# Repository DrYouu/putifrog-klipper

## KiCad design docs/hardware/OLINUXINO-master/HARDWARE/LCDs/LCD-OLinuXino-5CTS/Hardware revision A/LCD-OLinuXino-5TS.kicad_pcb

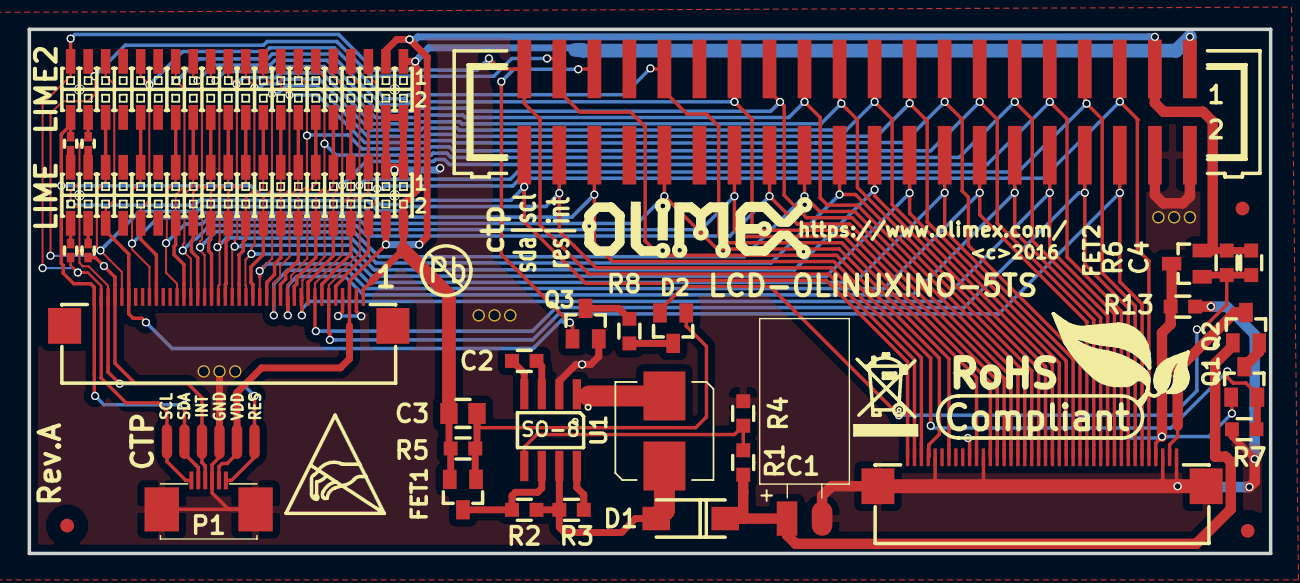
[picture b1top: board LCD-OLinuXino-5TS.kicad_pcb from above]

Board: 2 copper layers, 90.0 x 38.0 mm, 44 parts (0 on the bottom side), 54 nets.

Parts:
C1: 100uF/35V; CAP-EL-H-12x6.5
C2: 470pF; C_0603_5MIL_DWS
C3: 22uF/6.3V; C_0805_5MIL_DWS
C4: 1uF/6.3V; C_0603_5MIL_DWS
D1: 1N5819S(SS14); SMA-KA
D2: BAT54C; SOT23
FET1, FET2: IRML6402; SOT23
L1: 220uH/SD75; SD75
P1: CONN_01X06; FPV-WZB21-6-LF
P2: CONN_02X20; GBH-254-SMT-40
P3, P4: CONN_02X20; GPH127SMT-02X20(PA-V16X-2X20-LF)
P5, P6: CONN_01X40; FPV-WZA21-40-LF
P7: CONN_01X06; SIP6_SMD_50
Q1, Q3: DTC114YKA; SOT23
Q2: DTA114YKA; SOT23
R1, R5, R6, R13: 18K/1%; R_0603_5MIL_DWS
R2: 1R; R_0603_5MIL_DWS
R3: 150R; R_0603_5MIL_DWS
R4, R7, R8: 1.2K/1%; R_0603_5MIL_DWS
R9, R10, R11, R12: n.a(0R); J_0402_DWS
Ref**: Val**; via_09_07
Ref**#2, Ref**#3, Ref**#4, Ref**#5, Ref**#6, Ref**#7, Ref**#8, Ref**#9: Val**; via_09_07
Ref**#10: Val**; LOGO_ANTISTATIC_1
Ref**#11: Val**; LOGO_ROHS_1
U1: MC34063; SO-8

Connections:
+3.3VP: FET2.3, P6.4, P6.31, Q1.1, R13.1
/3.3V: C4.1, FET2.2, P1.2, P2.3, P3.3, P4.4, P5.3, P7.2, R6.1
/5V: C3.1, FET1.2, P2.1, P3.1, P4.2, P5.1, R5.1
/CTP_INT: P1.4, P2.37, P3.37, P5.37, P6.37, P7.4, R9.2
/CTP_RES: P1.1, P2.38, P3.38, P5.38, P6.38, P7.1, R10.1
/CTP_SCL: P1.6, P2.39, P3.39, P5.39, P6.39, P7.6, R11.2
/CTP_SDA: P1.5, P2.40, P3.40, P5.40, P6.40, P7.5, R12.1
/LCD_B0: P2.21, P3.21, P4.22, P5.21, P6.21
/LCD_B1: P2.22, P3.22, P4.21, P5.22, P6.22
/LCD_B2: P2.23, P3.23, P4.24, P5.23, P6.23
/LCD_B3: P2.24, P3.24, P4.23, P5.24, P6.24
/LCD_B4: P2.25, P3.25, P4.26, P5.25, P6.25
/LCD_B5: P2.26, P3.26, P4.25, P5.26, P6.26
/LCD_B6: P2.27, P3.27, P4.28, P5.27, P6.27
/LCD_B7: P2.28, P3.28, P4.27, P5.28, P6.28
/LCD_BKL: P2.36, P3.36, P4.35, P5.36, Q1.2, R7.1
/LCD_CLK: P2.31, P3.31, P4.32, P5.31, P6.30
/LCD_DE: P2.32, P3.32, P4.31, P5.32, P6.34
/LCD_G0: P2.13, P3.13, P4.14, P5.13, P6.13
/LCD_G1: P2.14, P3.14, P4.13, P5.14, P6.14
/LCD_G2: P2.15, P3.15, P4.16, P5.15, P6.15
/LCD_G3: P2.16, P3.16, P4.15, P5.16, P6.16
/LCD_G4: P2.17, P3.17, P4.18, P5.17, P6.17
/LCD_G5: P2.18, P3.18, P4.17, P5.18, P6.18
/LCD_G6: P2.19, P3.19, P4.20, P5.19, P6.19
/LCD_G7: P2.20, P3.20, P4.19, P5.20, P6.20
/LCD_PWRE: P2.35, P3.35, P4.36, P5.35, Q3.1
/LCD_R0: P2.5, P3.5, P4.6, P5.5, P6.5
/LCD_R1: P2.6, P3.6, P4.5, P5.6, P6.6
/LCD_R2: P2.7, P3.7, P4.8, P5.7, P6.7
/LCD_R3: P2.8, P3.8, P4.7, P5.8, P6.8
/LCD_R4: P2.9, P3.9, P4.10, P5.9, P6.9
/LCD_R5: P2.10, P3.10, P4.9, P5.10, P6.10
/LCD_R6: P2.11, P3.11, P4.12, P5.11, P6.11
/LCD_R7: P2.12, P3.12, P4.11, P5.12, P6.12
GND: C1.2, P1.3, P1.P1, P1.P2, P2.2, P2.4, P3.2, P3.4, P4.1, P4.3, P5.2, P5.4, P6.1, P6.3, P6.29, P6.36, P6.P1, P6.P2, P7.3, Q3.2, R4.2, R7.2, R13.2, Ref**.0, Ref**#2.0, Ref**#3.0, Ref**#4.0, Ref**#5.0, Ref**#6.0, Ref**#7.0, Ref**#8.0, Ref**#9.0, U1.2
unnamed: C1.1, D1.1, Q2.1, R1.1
unnamed: C2.1, U1.3
unnamed: C2.2, U1.4
unnamed: C3.2, D2.1, FET1.1, R5.2
unnamed: C4.2, D2.2, FET2.1, R6.2
unnamed: D1.2, L1.1, R2.2, R3.1, U1.7
unnamed: D2.3, R8.1
unnamed: L1.2, U1.1
unnamed: P4.37, R10.2
unnamed: P4.38, R9.1
unnamed: P4.39, R12.2
unnamed: P4.40, R11.1
unnamed: Q1.3, Q2.2
unnamed: Q3.3, R8.2
unnamed: R1.2, R4.1, U1.5
unnamed: R3.2, U1.8
VCOM: FET1.3, R2.1, U1.6
VLED: P6.2, Q2.3

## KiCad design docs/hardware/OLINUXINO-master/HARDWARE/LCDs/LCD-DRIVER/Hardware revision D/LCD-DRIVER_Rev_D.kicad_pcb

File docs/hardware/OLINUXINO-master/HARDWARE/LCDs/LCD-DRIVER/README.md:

LCD-DRIVER is a common LCD board used in some Olimex displays. It is important to notice that depending on the size of the display and the type of touschreen 
used the LCD_DRIVER board would be configured dirrently. Refer to the labes in the schematic and also refer to the bill of materials (BOM) for the different configurations.

List of boards using LCD-DRIVER as of 09.07.2025:

- LCD-OLinuXino-4.3RTS

- LCD-OLinuXino-7CTS

- LCD-OLinuXino-7RTS

- LCD-OLinuXino-10

- LCD-OLinuXino-10CTS

- LCD-OLinuXino-10RTS

All other LCDs use specific own specific boards (e.g. not LCD-DRIVER).

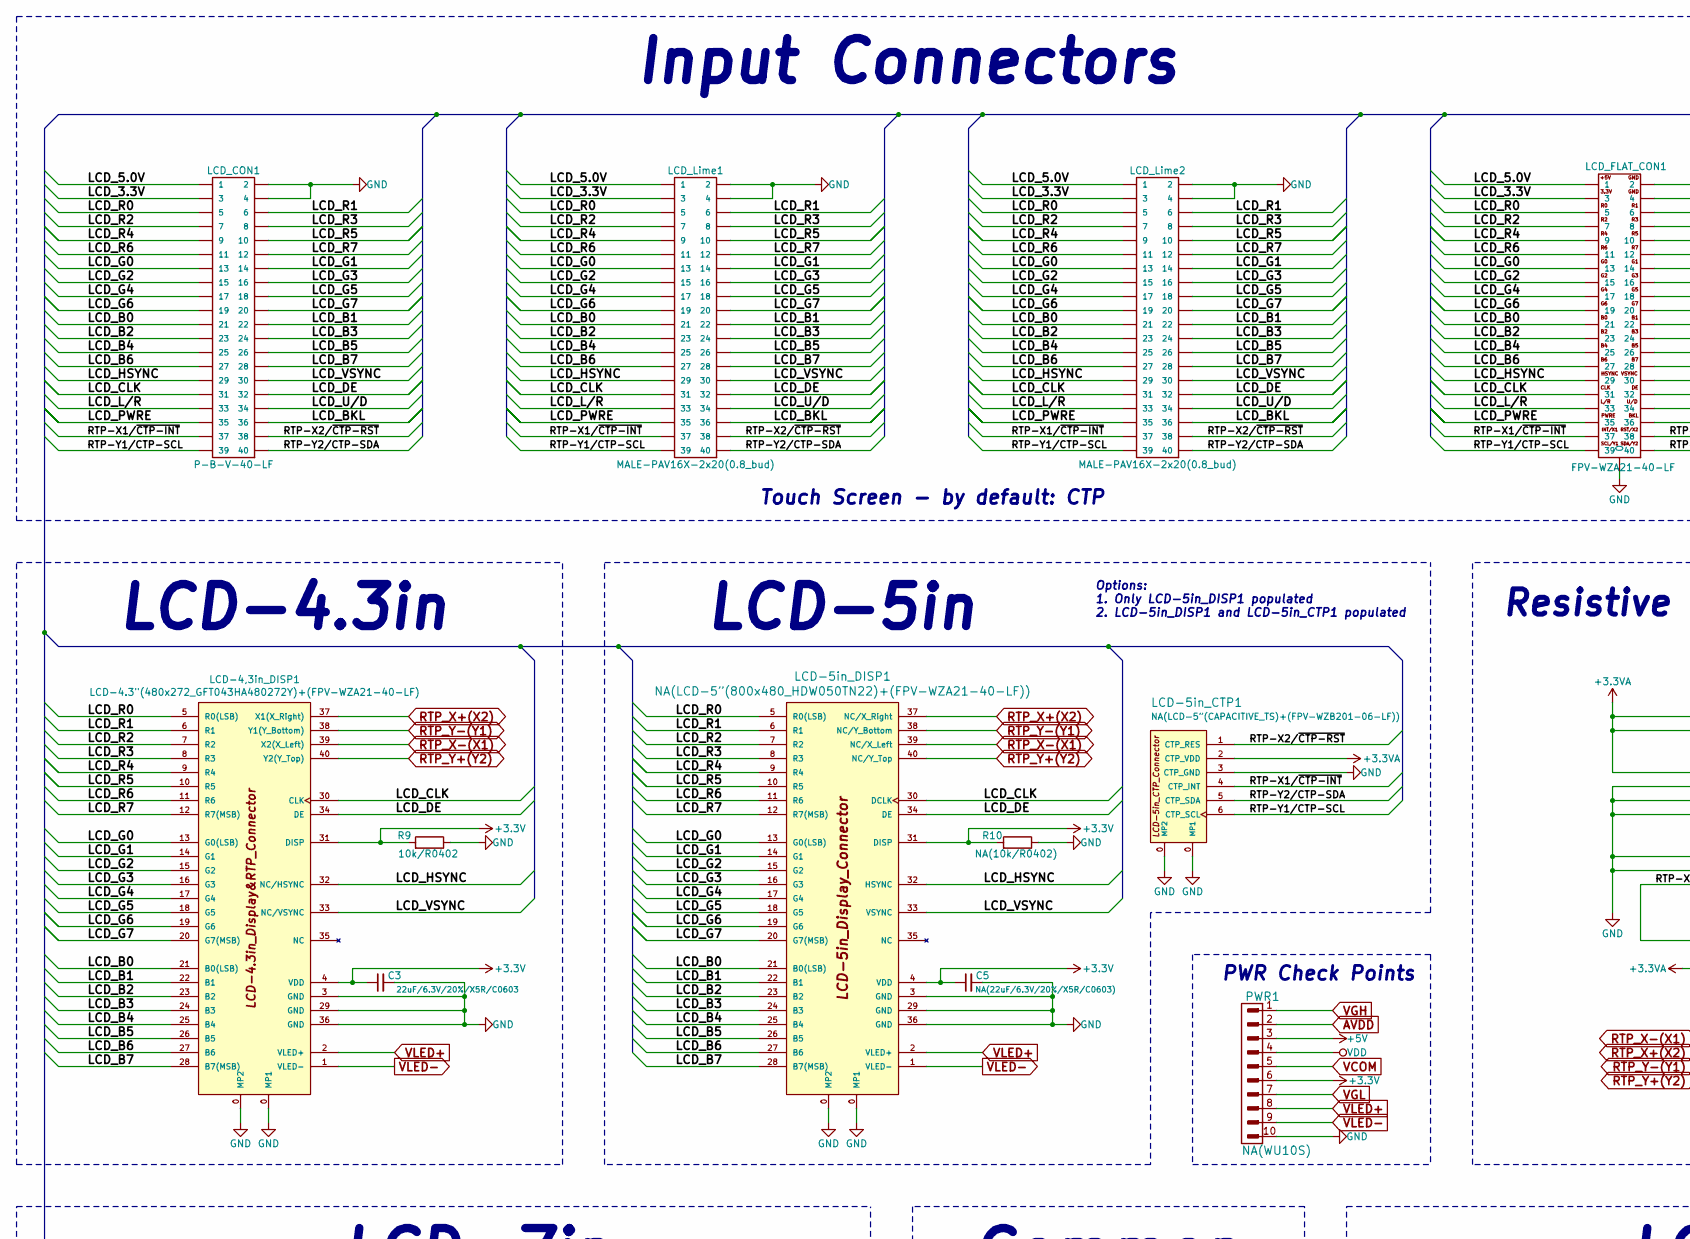
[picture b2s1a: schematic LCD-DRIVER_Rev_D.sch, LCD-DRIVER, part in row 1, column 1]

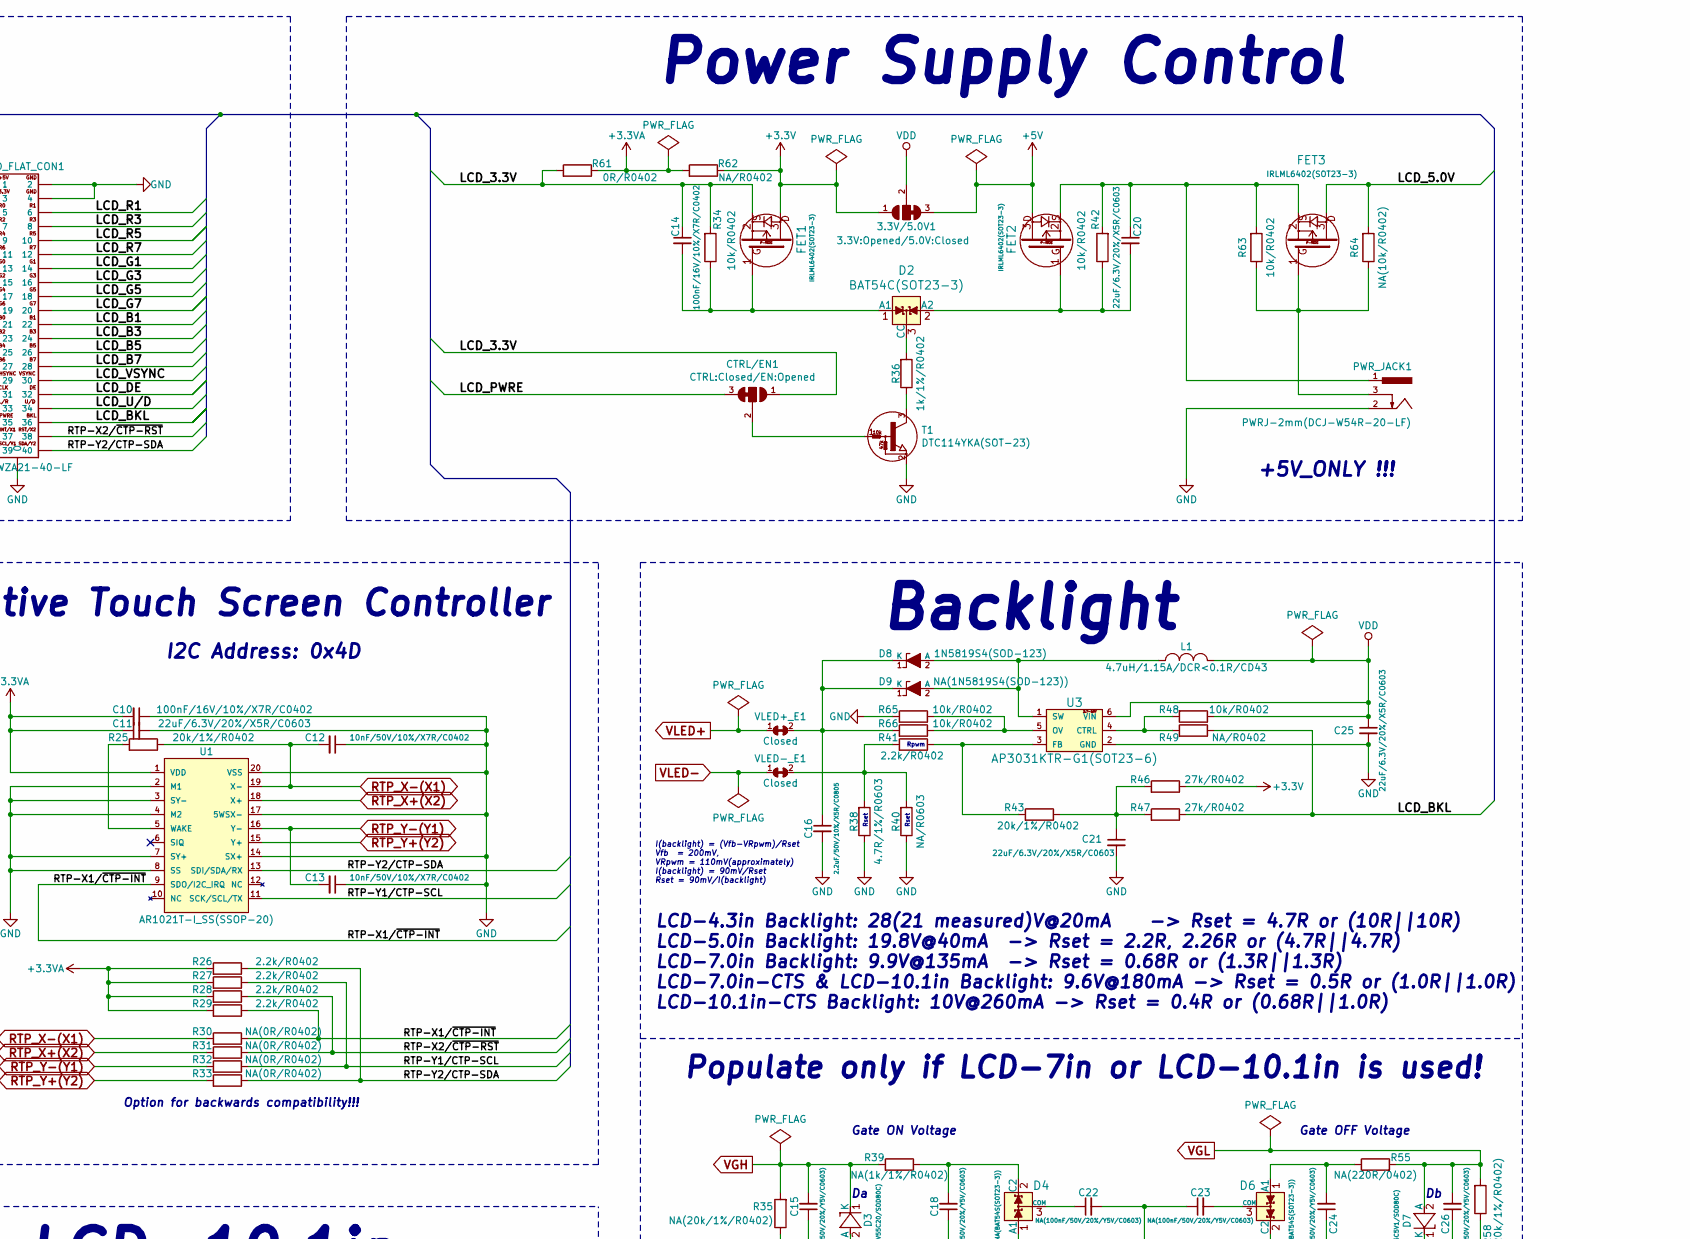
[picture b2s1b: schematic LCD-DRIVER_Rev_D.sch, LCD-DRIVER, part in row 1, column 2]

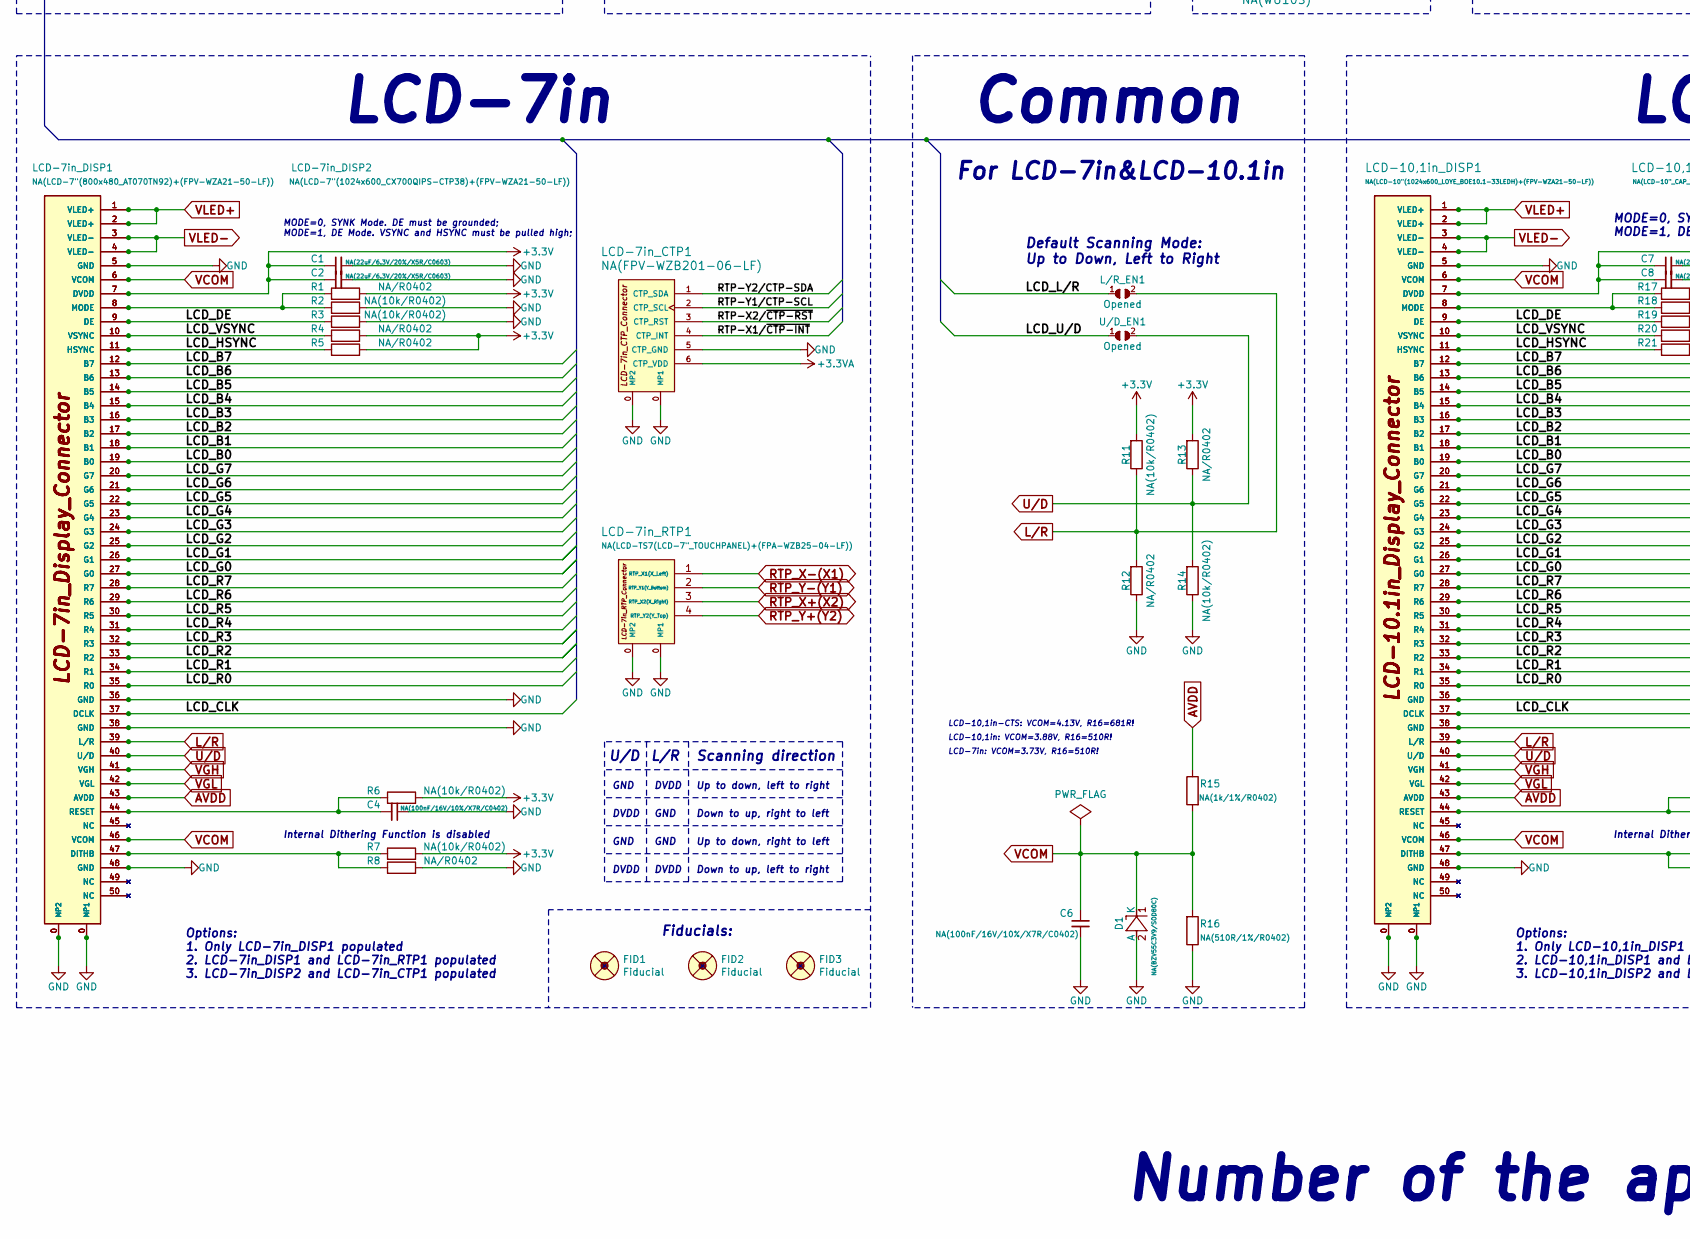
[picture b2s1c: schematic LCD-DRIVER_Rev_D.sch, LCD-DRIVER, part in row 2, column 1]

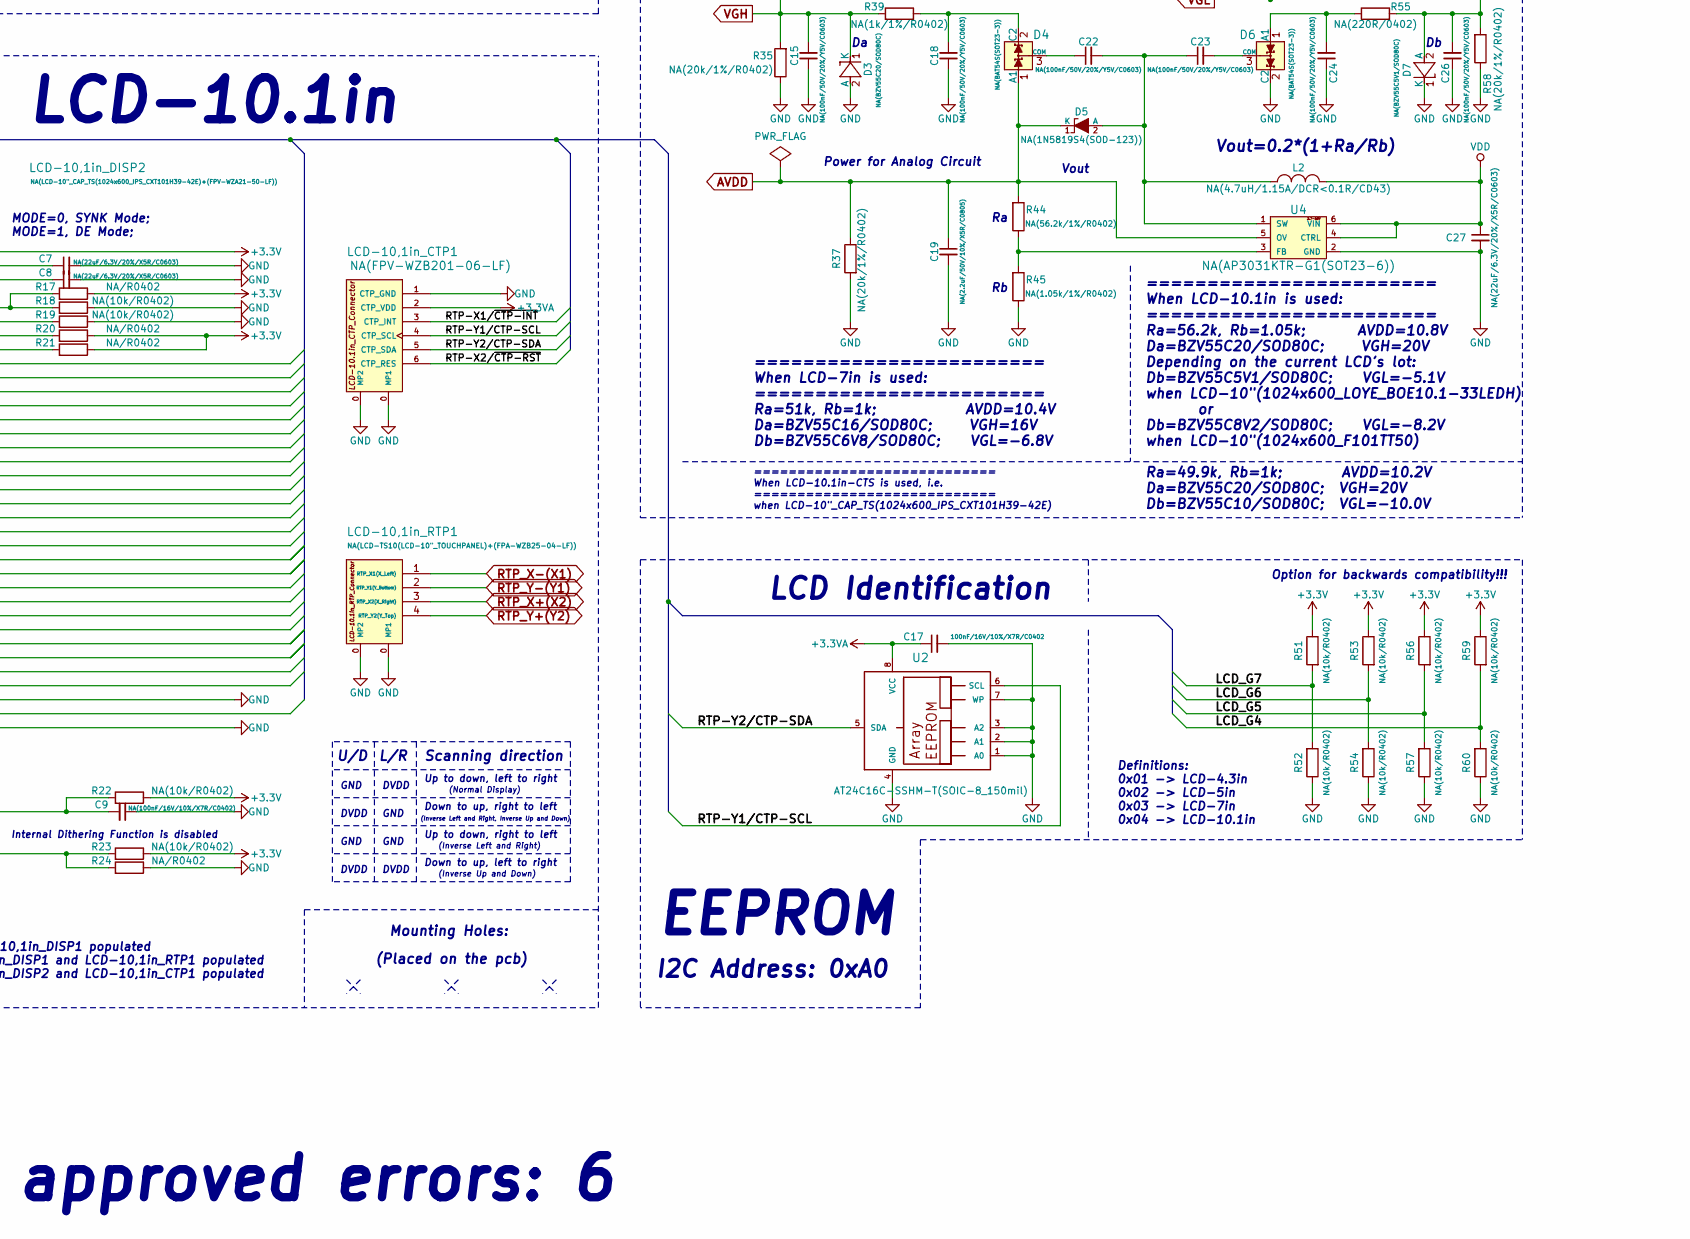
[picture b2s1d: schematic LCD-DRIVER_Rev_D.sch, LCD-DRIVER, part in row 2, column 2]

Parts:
3.3V/5.0V1: 3.3V:Opened/5.0V:Closed; SJ_2_SMALL_23_TIED
C1, C2, C5, C7, C8, C27: NA(22uF/6.3V/20%/X5R/C0603); C_0603_5MIL_DWS
C3, C11, C20, C21, C25: 22uF/6.3V/20%/X5R/C0603; C_0603_5MIL_DWS
C4, C6, C9: NA(100nF/16V/10%/X7R/C0402); C_0402_5MIL_DWS
C10, C14, C17: 100nF/16V/10%/X7R/C0402; C_0402_5MIL_DWS
C12, C13: 10nF/50V/10%/X7R/C0402; C_0402_5MIL_DWS
C15, C18, C22, C23, C24, C26: NA(100nF/50V/20%/Y5V/C0603); C_0603_5MIL_DWS
C16: 2.2uF/50V/10%/X5R/C0805; C_0805_5MIL_DWS
C19: NA(2.2uF/50V/10%/X5R/C0805); C_0805_5MIL_DWS
CTRL/EN1: CTRL:Closed/EN:Opened; SJ_2_SMALL_23_TIED
D1: NA(BZV55C3V9/SOD80C); SOD80C-4148-KA
D2: BAT54C(SOT23-3); SOT23-3
D3: NA(BZV55C20/SOD80C); SOD80C-4148-KA
D4, D6: NA(BAT54S(SOT23-3)); SOT23-3
D5, D9: NA(1N5819S4(SOD-123)); SOD-123_1C-2A_KA
D7: NA(BZV55C5V1/SOD80C); SOD80C-4148-KA
D8: 1N5819S4(SOD-123); SOD-123_1C-2A_KA
FET1, FET2, FET3: IRLML6402(SOT23-3); SOT23
FID1, FID2, FID3: Fiducial; Fiducial1x3
L1: 4.7uH/1.15A/DCR<0.1R/CD43; CD42(43)
L2: NA(4.7uH/1.15A/DCR<0.1R/CD43); CD42(43)
L/R_EN1: Opened; SJ
LCD-4,3in_DISP1: LCD-4.3\"(480x272_GFT043HA480272Y)+(FPV-WZA21-40-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; FPV-WZA21-40-LF
LCD-5in_CTP1: NA(LCD-5”(CAPACITIVE_TS)+(FPV-WZB201-06-LF)); FPV-WZB201-06-LF
LCD-5in_DISP1: NA(LCD-5”(800x480_HDW050TN22)+(FPV-WZA21-40-LF)); FPV-WZA21-40-LF
LCD-7in_CTP1, LCD-10,1in_CTP1: NA(FPV-WZB201-06-LF); FPV-WZB201-06-LF
LCD-7in_DISP1: NA(LCD-7\"(800x480_AT070TN92)+(FPV-WZA21-50-LF)); FPV-WZA21-50-LF
LCD-7in_DISP2: NA(LCD-7\"(1024x600_CX700QIPS-CTP38)+(FPV-WZA21-5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; FPV-WZA21-50-LF
LCD-7in_RTP1: NA(LCD-TS7(LCD-7\"_TOUCHPANEL)+(FPA-WZB25-04-LF)); FPA-WZB25-04-LF
LCD-10,1in_DISP1: NA(LCD-10\"(1024x600_LOYE_BOE10.1-33LEDH)+(FPV-WZ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; FPV-WZA21-50-LF
LCD-10,1in_DISP2: NA(LCD-10\"_CAP_TS(1024x600_IPS_CXT101H39-42E)+(F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; FPV-WZA21-50-LF
LCD-10,1in_RTP1: NA(LCD-TS10(LCD-10\"_TOUCHPANEL)+(FPA-WZB25-04-LF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; FPA-WZB25-04-LF
LCD_CON1: P-B-V-40-LF; GBH254SMT-40
LCD_FLAT_CON1: FPV-WZA21-40-LF
LCD_Lime1: MALE-PAV16X-2x20(0.8_bud); GPCB127SMT-02X20(YA-V36P-2X20-LF)_Drill_0.9mm
LCD_Lime2: MALE-PAV16X-2x20(0.8_bud); GPH127SMT-02X20(PA-V16X-2X20-LF)_Drill_0.9mm
PWR1: NA(WU10S); WU10S
PWR_JACK1: PWRJ-2mm(DCJ-W54R-20-LF)
R1, R4, R5, R8, R12, R13, R17, R20, R21, R24, R49, R62: NA/R0402; R_0402_5MIL_DWS
R2, R3, R6, R7, R10, R11, R14, R18, R19, R22, R23, R51, R52, R53, R54, R56, R57, R59, R60, R64: NA(10k/R0402); R_0402_5MIL_DWS
R9, R34, R42, R48, R63, R65, R66: 10k/R0402; R_0402_5MIL_DWS
R15, R39: NA(1k/1%/R0402); R_0402_5MIL_DWS
R16: NA(510R/1%/R0402); R_0402_5MIL_DWS
R25, R43: 20k/1%/R0402; R_0402_5MIL_DWS
R26, R27, R28, R29, R41: 2.2k/R0402; R_0402_5MIL_DWS
R30, R31, R32, R33: NA(0R/R0402); R_0402_5MIL_DWS
R35, R37, R58: NA(20k/1%/R0402); R_0402_5MIL_DWS
R36: 1k/1%/R0402; R_0402_5MIL_DWS
R38: 4.7R/1%/R0603; R_0603_5MIL_DWS
R40: NA/R0603; R_0603_5MIL_DWS
R44: NA(56.2k/1%/R0402); R_0402_5MIL_DWS
R45: NA(1.05k/1%/R0402); R_0402_5MIL_DWS
R46, R47: 27k/R0402; R_0402_5MIL_DWS
R55: NA(220R/0402); R_0402_5MIL_DWS
R61: 0R/R0402; R_0402_5MIL_DWS
T1: DTC114YKA(SOT-23); SOT23
U1: AR1021T-I_SS(SSOP-20); SSOP-20W
U2: AT24C16C-SSHM-T(SOIC-8_150mil); SOIC-8_150mil
U3: AP3031KTR-G1(SOT23-6); SOT23-6
U4: NA(AP3031KTR-G1(SOT23-6)); SOT23-6
U/D_EN1: Opened; SJ
VLED+_E1: Closed; SJ_Closed
VLED-_E1: Closed; SJ_Closed

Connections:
+3.3VA: C10.2, C11.1, C17.1, LCD-5in_CTP1.2 (CTP_VDD), LCD-7in_CTP1.6 (CTP_VDD), LCD-10,1in_CTP1.2 (CTP_VDD), R26.2, R27.2, R28.2, R29.2, R61.1, R62.2, U1.1 (VDD), U2.8 (VCC)
+3V3: 3.3V/5.0V1.1, C1.1, C2.1, C3.1, C5.1, C7.1, C8.1, FET1.3, LCD-4,3in_DISP1.4 (VDD), LCD-4,3in_DISP1.31 (DISP), LCD-5in_DISP1.4 (VDD), LCD-5in_DISP1.31 (DISP), LCD-7in_DISP1.7 (DVDD), LCD-7in_DISP2.7 (DVDD), LCD-10,1in_DISP1.7 (DVDD), LCD-10,1in_DISP2.7 (DVDD), PWR1.6, R1.1, R4.1, R5.1, R6.1, R7.1, R9.2, R10.2, R11.2, R13.2, R17.1, R20.1, R21.1, R22.1, R23.1, R46.1, R51.1, R53.1, R56.1, R59.1, R62.1
+5V: 3.3V/5.0V1.3, FET2.3, PWR1.3
/LCD_3.3V: C14.1, CTRL/EN1.1, FET1.2, LCD_CON1.3, LCD_FLAT_CON1.3, LCD_Lime1.3, LCD_Lime2.3, R34.2, R61.2
/LCD_5.0V: FET3.3, LCD_CON1.1, LCD_FLAT_CON1.1, LCD_Lime1.1, LCD_Lime2.1, R64.2
/LCD_B0: LCD-4,3in_DISP1.21 (B0(LSB)), LCD-5in_DISP1.21 (B0(LSB)), LCD-7in_DISP1.19 (B0), LCD-7in_DISP2.19 (B0), LCD-10,1in_DISP1.19 (B0), LCD-10,1in_DISP2.19 (B0), LCD_CON1.21, LCD_FLAT_CON1.21, LCD_Lime1.21, LCD_Lime2.21
/LCD_B1: LCD-4,3in_DISP1.22 (B1), LCD-5in_DISP1.22 (B1), LCD-7in_DISP1.18 (B1), LCD-7in_DISP2.18 (B1), LCD-10,1in_DISP1.18 (B1), LCD-10,1in_DISP2.18 (B1), LCD_CON1.22, LCD_FLAT_CON1.22, LCD_Lime1.22, LCD_Lime2.22
/LCD_B2: LCD-4,3in_DISP1.23 (B2), LCD-5in_DISP1.23 (B2), LCD-7in_DISP1.17 (B2), LCD-7in_DISP2.17 (B2), LCD-10,1in_DISP1.17 (B2), LCD-10,1in_DISP2.17 (B2), LCD_CON1.23, LCD_FLAT_CON1.23, LCD_Lime1.23, LCD_Lime2.23
/LCD_B3: LCD-4,3in_DISP1.24 (B3), LCD-5in_DISP1.24 (B3), LCD-7in_DISP1.16 (B3), LCD-7in_DISP2.16 (B3), LCD-10,1in_DISP1.16 (B3), LCD-10,1in_DISP2.16 (B3), LCD_CON1.24, LCD_FLAT_CON1.24, LCD_Lime1.24, LCD_Lime2.24
/LCD_B4: LCD-4,3in_DISP1.25 (B4), LCD-5in_DISP1.25 (B4), LCD-7in_DISP1.15 (B4), LCD-7in_DISP2.15 (B4), LCD-10,1in_DISP1.15 (B4), LCD-10,1in_DISP2.15 (B4), LCD_CON1.25, LCD_FLAT_CON1.25, LCD_Lime1.25, LCD_Lime2.25
/LCD_B5: LCD-4,3in_DISP1.26 (B5), LCD-5in_DISP1.26 (B5), LCD-7in_DISP1.14 (B5), LCD-7in_DISP2.14 (B5), LCD-10,1in_DISP1.14 (B5), LCD-10,1in_DISP2.14 (B5), LCD_CON1.26, LCD_FLAT_CON1.26, LCD_Lime1.26, LCD_Lime2.26
/LCD_B6: LCD-4,3in_DISP1.27 (B6), LCD-5in_DISP1.27 (B6), LCD-7in_DISP1.13 (B6), LCD-7in_DISP2.13 (B6), LCD-10,1in_DISP1.13 (B6), LCD-10,1in_DISP2.13 (B6), LCD_CON1.27, LCD_FLAT_CON1.27, LCD_Lime1.27, LCD_Lime2.27
/LCD_B7: LCD-4,3in_DISP1.28 (B7(MSB)), LCD-5in_DISP1.28 (B7(MSB)), LCD-7in_DISP1.12 (B7), LCD-7in_DISP2.12 (B7), LCD-10,1in_DISP1.12 (B7), LCD-10,1in_DISP2.12 (B7), LCD_CON1.28, LCD_FLAT_CON1.28, LCD_Lime1.28, LCD_Lime2.28
/LCD_BKL: LCD_CON1.36, LCD_FLAT_CON1.36, LCD_Lime1.36, LCD_Lime2.36, R47.1, R49.1
/LCD_CLK: LCD-4,3in_DISP1.30 (CLK), LCD-5in_DISP1.30 (DCLK), LCD-7in_DISP1.37 (DCLK), LCD-7in_DISP2.37 (DCLK), LCD-10,1in_DISP1.37 (DCLK), LCD-10,1in_DISP2.37 (DCLK), LCD_CON1.31, LCD_FLAT_CON1.31, LCD_Lime1.31, LCD_Lime2.31
/LCD_DE: LCD-4,3in_DISP1.34 (DE), LCD-5in_DISP1.34 (DE), LCD-7in_DISP1.9 (DE), LCD-7in_DISP2.9 (DE), LCD-10,1in_DISP1.9 (DE), LCD-10,1in_DISP2.9 (DE), LCD_CON1.32, LCD_FLAT_CON1.32, LCD_Lime1.32, LCD_Lime2.32, R3.2, R19.2
/LCD_G0: LCD-4,3in_DISP1.13 (G0(LSB)), LCD-5in_DISP1.13 (G0(LSB)), LCD-7in_DISP1.27 (G0), LCD-7in_DISP2.27 (G0), LCD-10,1in_DISP1.27 (G0), LCD-10,1in_DISP2.27 (G0), LCD_CON1.13, LCD_FLAT_CON1.13, LCD_Lime1.13, LCD_Lime2.13
/LCD_G1: LCD-4,3in_DISP1.14 (G1), LCD-5in_DISP1.14 (G1), LCD-7in_DISP1.26 (G1), LCD-7in_DISP2.26 (G1), LCD-10,1in_DISP1.26 (G1), LCD-10,1in_DISP2.26 (G1), LCD_CON1.14, LCD_FLAT_CON1.14, LCD_Lime1.14, LCD_Lime2.14
/LCD_G2: LCD-4,3in_DISP1.15 (G2), LCD-5in_DISP1.15 (G2), LCD-7in_DISP1.25 (G2), LCD-7in_DISP2.25 (G2), LCD-10,1in_DISP1.25 (G2), LCD-10,1in_DISP2.25 (G2), LCD_CON1.15, LCD_FLAT_CON1.15, LCD_Lime1.15, LCD_Lime2.15
/LCD_G3: LCD-4,3in_DISP1.16 (G3), LCD-5in_DISP1.16 (G3), LCD-7in_DISP1.24 (G3), LCD-7in_DISP2.24 (G3), LCD-10,1in_DISP1.24 (G3), LCD-10,1in_DISP2.24 (G3), LCD_CON1.16, LCD_FLAT_CON1.16, LCD_Lime1.16, LCD_Lime2.16
/LCD_G4: LCD-4,3in_DISP1.17 (G4), LCD-5in_DISP1.17 (G4), LCD-7in_DISP1.23 (G4), LCD-7in_DISP2.23 (G4), LCD-10,1in_DISP1.23 (G4), LCD-10,1in_DISP2.23 (G4), LCD_CON1.17, LCD_FLAT_CON1.17, LCD_Lime1.17, LCD_Lime2.17, R59.2, R60.2
/LCD_G5: LCD-4,3in_DISP1.18 (G5), LCD-5in_DISP1.18 (G5), LCD-7in_DISP1.22 (G5), LCD-7in_DISP2.22 (G5), LCD-10,1in_DISP1.22 (G5), LCD-10,1in_DISP2.22 (G5), LCD_CON1.18, LCD_FLAT_CON1.18, LCD_Lime1.18, LCD_Lime2.18, R56.2, R57.2
/LCD_G6: LCD-4,3in_DISP1.19 (G6), LCD-5in_DISP1.19 (G6), LCD-7in_DISP1.21 (G6), LCD-7in_DISP2.21 (G6), LCD-10,1in_DISP1.21 (G6), LCD-10,1in_DISP2.21 (G6), LCD_CON1.19, LCD_FLAT_CON1.19, LCD_Lime1.19, LCD_Lime2.19, R53.2, R54.2
/LCD_G7: LCD-4,3in_DISP1.20 (G7(MSB)), LCD-5in_DISP1.20 (G7(MSB)), LCD-7in_DISP1.20 (G7), LCD-7in_DISP2.20 (G7), LCD-10,1in_DISP1.20 (G7), LCD-10,1in_DISP2.20 (G7), LCD_CON1.20, LCD_FLAT_CON1.20, LCD_Lime1.20, LCD_Lime2.20, R51.2, R52.2
/LCD_HSYNC: LCD-4,3in_DISP1.32 (NC/HSYNC), LCD-5in_DISP1.32 (HSYNC), LCD-7in_DISP1.11 (HSYNC), LCD-7in_DISP2.11 (HSYNC), LCD-10,1in_DISP1.11 (HSYNC), LCD-10,1in_DISP2.11 (HSYNC), LCD_CON1.29, LCD_FLAT_CON1.29, LCD_Lime1.29, LCD_Lime2.29, R5.2, R21.2
/LCD_L/R: L/R_EN1.1, LCD_CON1.33, LCD_FLAT_CON1.33, LCD_Lime1.33, LCD_Lime2.33
/LCD_PWRE: CTRL/EN1.3, LCD_CON1.35, LCD_FLAT_CON1.35, LCD_Lime1.35, LCD_Lime2.35
/LCD_R0: LCD-4,3in_DISP1.5 (R0(LSB)), LCD-5in_DISP1.5 (R0(LSB)), LCD-7in_DISP1.35 (R0), LCD-7in_DISP2.35 (R0), LCD-10,1in_DISP1.35 (R0), LCD-10,1in_DISP2.35 (R0), LCD_CON1.5, LCD_FLAT_CON1.5, LCD_Lime1.5, LCD_Lime2.5
/LCD_R1: LCD-4,3in_DISP1.6 (R1), LCD-5in_DISP1.6 (R1), LCD-7in_DISP1.34 (R1), LCD-7in_DISP2.34 (R1), LCD-10,1in_DISP1.34 (R1), LCD-10,1in_DISP2.34 (R1), LCD_CON1.6, LCD_FLAT_CON1.6, LCD_Lime1.6, LCD_Lime2.6
/LCD_R2: LCD-4,3in_DISP1.7 (R2), LCD-5in_DISP1.7 (R2), LCD-7in_DISP1.33 (R2), LCD-7in_DISP2.33 (R2), LCD-10,1in_DISP1.33 (R2), LCD-10,1in_DISP2.33 (R2), LCD_CON1.7, LCD_FLAT_CON1.7, LCD_Lime1.7, LCD_Lime2.7
/LCD_R3: LCD-4,3in_DISP1.8 (R3), LCD-5in_DISP1.8 (R3), LCD-7in_DISP1.32 (R3), LCD-7in_DISP2.32 (R3), LCD-10,1in_DISP1.32 (R3), LCD-10,1in_DISP2.32 (R3), LCD_CON1.8, LCD_FLAT_CON1.8, LCD_Lime1.8, LCD_Lime2.8
/LCD_R4: LCD-4,3in_DISP1.9 (R4), LCD-5in_DISP1.9 (R4), LCD-7in_DISP1.31 (R4), LCD-7in_DISP2.31 (R4), LCD-10,1in_DISP1.31 (R4), LCD-10,1in_DISP2.31 (R4), LCD_CON1.9, LCD_FLAT_CON1.9, LCD_Lime1.9, LCD_Lime2.9
/LCD_R5: LCD-4,3in_DISP1.10 (R5), LCD-5in_DISP1.10 (R5), LCD-7in_DISP1.30 (R5), LCD-7in_DISP2.30 (R5), LCD-10,1in_DISP1.30 (R5), LCD-10,1in_DISP2.30 (R5), LCD_CON1.10, LCD_FLAT_CON1.10, LCD_Lime1.10, LCD_Lime2.10
/LCD_R6: LCD-4,3in_DISP1.11 (R6), LCD-5in_DISP1.11 (R6), LCD-7in_DISP1.29 (R6), LCD-7in_DISP2.29 (R6), LCD-10,1in_DISP1.29 (R6), LCD-10,1in_DISP2.29 (R6), LCD_CON1.11, LCD_FLAT_CON1.11, LCD_Lime1.11, LCD_Lime2.11
/LCD_R7: LCD-4,3in_DISP1.12 (R7(MSB)), LCD-5in_DISP1.12 (R7(MSB)), LCD-7in_DISP1.28 (R7), LCD-7in_DISP2.28 (R7), LCD-10,1in_DISP1.28 (R7), LCD-10,1in_DISP2.28 (R7), LCD_CON1.12, LCD_FLAT_CON1.12, LCD_Lime1.12, LCD_Lime2.12
/LCD_U/D: LCD_CON1.34, LCD_FLAT_CON1.34, LCD_Lime1.34, LCD_Lime2.34, U/D_EN1.1
/LCD_VSYNC: LCD-4,3in_DISP1.33 (NC/VSYNC), LCD-5in_DISP1.33 (VSYNC), LCD-7in_DISP1.10 (VSYNC), LCD-7in_DISP2.10 (VSYNC), LCD-10,1in_DISP1.10 (VSYNC), LCD-10,1in_DISP2.10 (VSYNC), LCD_CON1.30, LCD_FLAT_CON1.30, LCD_Lime1.30, LCD_Lime2.30, R4.2, R20.2
/RTP-X1/~CTP-INT: LCD-5in_CTP1.4 (CTP_INT), LCD-7in_CTP1.4 (CTP_INT), LCD-10,1in_CTP1.3 (CTP_INT), LCD_CON1.37, LCD_FLAT_CON1.37, LCD_Lime1.37, LCD_Lime2.37, R29.1, R30.1, U1.9 (SDO/I2C_IRQ)
/RTP-X2/~CTP-RST: LCD-5in_CTP1.1 (CTP_RES), LCD-7in_CTP1.3 (CTP_RST), LCD-10,1in_CTP1.6 (CTP_RES), LCD_CON1.38, LCD_FLAT_CON1.38, LCD_Lime1.38, LCD_Lime2.38, R28.1, R31.1
/RTP-Y1/CTP-SCL: LCD-5in_CTP1.6 (CTP_SCL), LCD-7in_CTP1.2 (CTP_SCL), LCD-10,1in_CTP1.4 (CTP_SCL), LCD_CON1.39, LCD_FLAT_CON1.39, LCD_Lime1.39, LCD_Lime2.39, R27.1, R32.1, U1.11 (SCK/SCL/TX), U2.6 (SCL)
/RTP-Y2/CTP-SDA: LCD-5in_CTP1.5 (CTP_SDA), LCD-7in_CTP1.1 (CTP_SDA), LCD-10,1in_CTP1.5 (CTP_SDA), LCD_CON1.40, LCD_FLAT_CON1.40, LCD_Lime1.40, LCD_Lime2.40, R26.1, R33.1, U1.13 (SDI/SDA/RX), U2.5 (SDA)
AVDD: C19.1, D4.1 (A1), D5.1 (K), LCD-7in_DISP1.43 (AVDD), LCD-7in_DISP2.43 (AVDD), LCD-10,1in_DISP1.43 (AVDD), LCD-10,1in_DISP2.43 (AVDD), PWR1.2, R15.1, R37.1, R44.2, U4.5 (OV)
GND: C1.2, C2.2, C3.2, C4.1, C5.2, C6.2, C7.2, C8.2, C9.1, C10.1, C11.2, C12.1, C13.1, C15.1, C16.2, C17.2, C18.1, C19.2, C21.2, C24.1, C25.2, C26.1, C27.2, D1.2 (A), D3.2 (A), D6.2 (C2), D7.1 (K), LCD-4,3in_DISP1.0 (MP1), LCD-4,3in_DISP1.3 (GND), LCD-4,3in_DISP1.29 (GND), LCD-4,3in_DISP1.36 (GND), LCD-5in_CTP1.0 (MP1), LCD-5in_CTP1.3 (CTP_GND), LCD-5in_DISP1.0 (MP1), LCD-5in_DISP1.3 (GND), LCD-5in_DISP1.29 (GND), LCD-5in_DISP1.36 (GND), LCD-7in_CTP1.0 (MP1), LCD-7in_CTP1.5 (CTP_GND), LCD-7in_DISP1.0 (MP1), LCD-7in_DISP1.5 (GND), LCD-7in_DISP1.36 (GND), LCD-7in_DISP1.38 (GND), LCD-7in_DISP1.48 (GND), LCD-7in_DISP2.0 (MP1), LCD-7in_DISP2.5 (GND), LCD-7in_DISP2.36 (GND), LCD-7in_DISP2.38 (GND), LCD-7in_DISP2.48 (GND), LCD-7in_RTP1.0 (MP1), LCD-10,1in_CTP1.0 (MP1), LCD-10,1in_CTP1.1 (CTP_GND), LCD-10,1in_DISP1.0 (MP1), LCD-10,1in_DISP1.5 (GND), LCD-10,1in_DISP1.36 (GND), LCD-10,1in_DISP1.38 (GND), LCD-10,1in_DISP1.48 (GND), LCD-10,1in_DISP2.0 (MP1), LCD-10,1in_DISP2.5 (GND), LCD-10,1in_DISP2.36 (GND), LCD-10,1in_DISP2.38 (GND), LCD-10,1in_DISP2.48 (GND), LCD-10,1in_RTP1.0 (MP1), LCD_CON1.2, LCD_CON1.4, LCD_FLAT_CON1.0, LCD_FLAT_CON1.2, LCD_FLAT_CON1.4, LCD_Lime1.2, LCD_Lime1.4, LCD_Lime2.2, LCD_Lime2.4, PWR1.10, PWR_JACK1.2 (-), R2.1, R3.1, R8.1, R9.1, R10.1, R12.1, R14.1, R16.1, R18.1, R19.1, R24.1, R35.1, R37.2, R38.1, R40.1, R45.1, R52.1, R54.1, R57.1, R58.1, R60.1, R65.2, T1.2 (E), U1.2 (M1), U1.3 (SY-), U1.4 (M2), U1.7 (SY+), U1.8 (SS), U1.14 (SX+), U1.17 (5WSX-), U1.20 (VSS), U2.1 (A0), U2.2 (A1), U2.3 (A2), U2.4 (GND), U2.7 (WP), U3.2 (GND), U4.2 (GND)
L/R: L/R_EN1.2, LCD-7in_DISP1.39 (L/R), LCD-7in_DISP2.39 (L/R), LCD-10,1in_DISP1.39 (L/R), LCD-10,1in_DISP2.39 (L/R), R11.1, R12.2
unnamed: C4.2, LCD-7in_DISP1.44 (RESET), LCD-7in_DISP2.44 (RESET), R6.2
unnamed: C9.2, LCD-10,1in_DISP1.44 (RESET), LCD-10,1in_DISP2.44 (RESET), R22.2
unnamed: C14.2, D2.1 (A1), FET1.1, R34.1
unnamed: C16.1, D8.1 (K), D9.1 (K), R66.2, VLED+_E1.2
unnamed: C18.2, D4.2 (C2), R39.1
unnamed: C20.1, FET2.2, FET3.2, PWR_JACK1.1 (+), R42.2, R63.2
unnamed: C20.2, D2.2 (A2), FET2.1, R42.1
unnamed: C21.1, R43.1, R46.2, R47.2
unnamed: C22.1, D4.3 (COM)
unnamed: C22.2, C23.1, D5.2 (A), L2.1, U4.1 (SW)
unnamed: C23.2, D6.3 (COM)
unnamed: C24.2, D6.1 (A1), R55.1
unnamed: CTRL/EN1.2, T1.1 (B)
unnamed: D2.3 (CC), R36.2
unnamed: D8.2 (A), D9.2 (A), L1.1, U3.1 (SW)
unnamed: FET3.1, PWR_JACK1.3 (-), R63.1, R64.1
unnamed: LCD-7in_DISP1.8 (MODE), LCD-7in_DISP2.8 (MODE), R1.2, R2.2
unnamed: LCD-7in_DISP1.45 (NC), LCD-7in_DISP2.45 (NC)
unnamed: LCD-7in_DISP1.47 (DITHB), LCD-7in_DISP2.47 (DITHB), R7.2, R8.2
unnamed: LCD-7in_DISP1.49 (NC), LCD-7in_DISP2.49 (NC)
unnamed: LCD-7in_DISP1.50 (NC), LCD-7in_DISP2.50 (NC)
unnamed: LCD-10,1in_DISP1.8 (MODE), LCD-10,1in_DISP2.8 (MODE), R17.2, R18.2
unnamed: LCD-10,1in_DISP1.45 (NC), LCD-10,1in_DISP2.45 (NC)
unnamed: LCD-10,1in_DISP1.47 (DITHB), LCD-10,1in_DISP2.47 (DITHB), R23.2, R24.2
unnamed: LCD-10,1in_DISP1.49 (NC), LCD-10,1in_DISP2.49 (NC)
unnamed: LCD-10,1in_DISP1.50 (NC), LCD-10,1in_DISP2.50 (NC)
unnamed: R25.2, U1.5 (WAKE)
unnamed: R36.1, T1.3 (C)
unnamed: R38.2, R40.2, R41.2, VLED-_E1.2
unnamed: R41.1, R43.2, U3.3 (FB)
unnamed: R44.1, R45.2, U4.3 (FB)
unnamed: R48.2, R49.2, U3.4 (CTRL)
unnamed: R65.1, R66.1, U3.5 (OV)
RTP_X+(X2): LCD-4,3in_DISP1.37 (X1(X_Right)), LCD-5in_DISP1.37 (NC/X_Right), LCD-7in_RTP1.3 (RTP_X2(X_Right)), LCD-10,1in_RTP1.3 (RTP_X2(X_Right)), R31.2, U1.18 (X+)
RTP_X-(X1): C12.2, LCD-4,3in_DISP1.39 (X2(X_Left)), LCD-5in_DISP1.39 (NC/X_Left), LCD-7in_RTP1.1 (RTP_X1(X_Left)), LCD-10,1in_RTP1.1 (RTP_X1(X_Left)), R25.1, R30.2, U1.19 (X-)
RTP_Y+(Y2): LCD-4,3in_DISP1.40 (Y2(Y_Top)), LCD-5in_DISP1.40 (NC/Y_Top), LCD-7in_RTP1.4 (RTP_Y2(Y_Top)), LCD-10,1in_RTP1.4 (RTP_Y2(Y_Top)), R33.2, U1.15 (Y+)
RTP_Y-(Y1): C13.2, LCD-4,3in_DISP1.38 (Y1(Y_Bottom)), LCD-5in_DISP1.38 (NC/Y_Bottom), LCD-7in_RTP1.2 (RTP_Y1(Y_Bottom)), LCD-10,1in_RTP1.2 (RTP_Y1(Y_Bottom)), R32.2, U1.16 (Y-)
U/D: LCD-7in_DISP1.40 (U/D), LCD-7in_DISP2.40 (U/D), LCD-10,1in_DISP1.40 (U/D), LCD-10,1in_DISP2.40 (U/D), R13.1, R14.2, U/D_EN1.2
VCOM: C6.1, D1.1 (K), LCD-7in_DISP1.6 (VCOM), LCD-7in_DISP1.46 (VCOM), LCD-7in_DISP2.6 (VCOM), LCD-7in_DISP2.46 (VCOM), LCD-10,1in_DISP1.6 (VCOM), LCD-10,1in_DISP1.46 (VCOM), LCD-10,1in_DISP2.6 (VCOM), LCD-10,1in_DISP2.46 (VCOM), PWR1.5, R15.2, R16.2
VDD: 3.3V/5.0V1.2, C25.1, C27.1, L1.2, L2.2, PWR1.4, R48.1, U3.6 (VIN), U4.4 (CTRL), U4.6 (VIN)
VGH: C15.2, D3.1 (K), LCD-7in_DISP1.41 (VGH), LCD-7in_DISP2.41 (VGH), LCD-10,1in_DISP1.41 (VGH), LCD-10,1in_DISP2.41 (VGH), PWR1.1, R35.2, R39.2
VGL: C26.2, D7.2 (A), LCD-7in_DISP1.42 (VGL), LCD-7in_DISP2.42 (VGL), LCD-10,1in_DISP1.42 (VGL), LCD-10,1in_DISP2.42 (VGL), PWR1.7, R55.2, R58.2
VLED+: LCD-4,3in_DISP1.2 (VLED+), LCD-5in_DISP1.2 (VLED+), LCD-7in_DISP1.1 (VLED+), LCD-7in_DISP1.2 (VLED+), LCD-7in_DISP2.1 (VLED+), LCD-7in_DISP2.2 (VLED+), LCD-10,1in_DISP1.1 (VLED+), LCD-10,1in_DISP1.2 (VLED+), LCD-10,1in_DISP2.1 (VLED+), LCD-10,1in_DISP2.2 (VLED+), PWR1.8, VLED+_E1.1
VLED-: LCD-4,3in_DISP1.1 (VLED-), LCD-5in_DISP1.1 (VLED-), LCD-7in_DISP1.3 (VLED-), LCD-7in_DISP1.4 (VLED-), LCD-7in_DISP2.3 (VLED-), LCD-7in_DISP2.4 (VLED-), LCD-10,1in_DISP1.3 (VLED-), LCD-10,1in_DISP1.4 (VLED-), LCD-10,1in_DISP2.3 (VLED-), LCD-10,1in_DISP2.4 (VLED-), PWR1.9, VLED-_E1.1

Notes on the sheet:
I2C Address: 0xA0
EEPROM
LCD Identification
+5V_ONLY !!!
Input Connectors
Power Supply Control
LCD-4.3in Backlight: 28(21 measured)V@20mA -> Rset = 4.7R or (10R||10R) LCD-5.0in Backlight: 19.8V@40mA -> Rset = 2.2R, 2.26R or (4.7R||4.7R) LCD-7.0in Backlight: 9.9V@135mA -> Rset = 0.68R or (1.3R||1.3R) LCD-7.0in-CTS & LCD-10.1in Backlight: 9.6V@180mA -> Rset = 0.5R or (1.0R||1.0R) LCD-10.1in-CT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
Backlight
Rset
I(backlight) = (Vfb-VRpwm)/Rset Vfb = 200mV, VRpwm = 110mV(approximately) I(backlight) = 90mV/Rset Rset = 90mV/I(backlight)
LCD-4.3in
Resistive Touch Screen Controller
Touch Screen - by default: CTP
Option for backwards compatibility!!!
I2C Address: 0x4D
LCD-5in
LCD-7in
MODE=0, SYNK Mode. DE must be grounded; MODE=1, DE Mode. VSYNC and HSYNC must be pulled high;
Default Scanning Mode: Up to Down, Left to Right
Internal Dithering Function is disabled
LCD-7in: VCOM=3.73V, R16=510R!
Vout=0.2*(1+Ra/Rb)
Vout
======================== When LCD-7in is used: ======================== Ra=51k, Rb=1k; AVDD=10.4V Da=BZV55C16/SOD80C; VGH=16V Db=BZV55C6V8/SOD80C; VGL=-6.8V
Populate only if LCD-7in or LCD-10.1in is used!
======================== When LCD-10.1in is used: ======================== Ra=56.2k, Rb=1.05k; AVDD=10.8V Da=BZV55C20/SOD80C; VGH=20V Depending on the current LCD's lot: Db=BZV55C5V1/SOD80C; VGL=-5.1V when LCD-10"(1024x600_LOYE_BOE10.1-33LEDH) or Db=BZV55C8V2/SOD80C; VGL=-8.2V when LCD-10"(1024x600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
LCD-10.1in
Common
For LCD-7in&LCD-10.1in
Power for Analog Circuit
Gate ON Voltage
Gate OFF Voltage
Definitions: 0x01 -> LCD-4.3in 0x02 -> LCD-5in 0x03 -> LCD-7in 0x04 -> LCD-10.1in
Options: 1. Only LCD-7in_DISP1 populated 2. LCD-7in_DISP1 and LCD-7in_RTP1 populated 3. LCD-7in_DISP2 and LCD-7in_CTP1 populated
Options: 1. Only LCD-5in_DISP1 populated 2. LCD-5in_DISP1 and LCD-5in_CTP1 populated
PWR Check Points
Options: 1. Only LCD-10,1in_DISP1 populated 2. LCD-10,1in_DISP1 and LCD-10,1in_RTP1 populated 3. LCD-10,1in_DISP2 and LCD-10,1in_CTP1 populated
Up to down, left to right
Down to up, right to left
Up to down, right to left

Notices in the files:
docs/hardware/OLINUXINO-master/HARDWARE/LCDs/LCD-DRIVER/Hardware revision D/LCD-DRIVER_Rev_D.kicad_pcb:
(C) 2019
